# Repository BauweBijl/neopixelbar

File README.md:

# neopixelbar
Eagle files for a single sided 6 led's (WS2812B) PCB

This singlesided PCB design is for a neopixelbar with 6 WS2812B RGB led's (smd)...toner transfer method.

The WS2812B smd led's are soldered on the surface while the capacitors are tht and soldered on the bottom side of the board.

# Download and Print
Open the neonpixelbar.brd in Eagle and select the layers:

1. Top
2. Pads
3. Vias
4. Unrouted
5. Dimensions
6. Holes

Hit Ratsnest and print mirrored!

# Instructions
Build instructions with images follow later (todo)

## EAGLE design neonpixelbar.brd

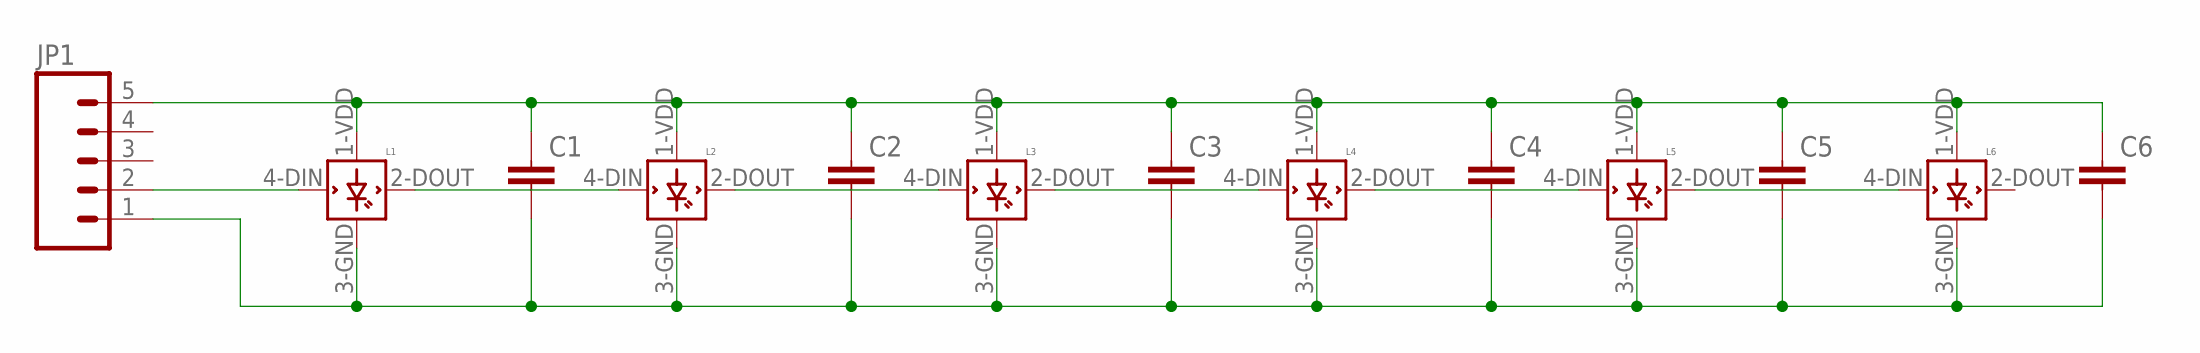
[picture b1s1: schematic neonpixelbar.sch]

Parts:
C1, C2, C3, C4, C5, C6: CAPPTH3; CAP-PTH-LARGE
JP1: M05PTH_LONGPADS; 1X05_LONGPADS
L1, L2, L3, L4, L5, L6: WS2812B

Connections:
GND: C1.2, C2.2, C3.2, C4.2, C5.2, C6.2, JP1.1, L1.3-GND (GND), L2.3-GND (GND), L3.3-GND (GND), L4.3-GND (GND), L5.3-GND (GND), L6.3-GND (GND)
unnamed: L1.2-DOUT (DOUT), L2.4-DIN (DIN)
unnamed: L2.2-DOUT (DOUT), L3.4-DIN (DIN)
unnamed: L3.2-DOUT (DOUT), L4.4-DIN (DIN)
unnamed: L4.2-DOUT (DOUT), L5.4-DIN (DIN)
unnamed: L5.2-DOUT (DOUT), L6.4-DIN (DIN)
unnamed: JP1.2, L1.4-DIN (DIN)
VDD: C1.1, C2.1, C3.1, C4.1, C5.1, C6.1, JP1.5, L1.1-VDD (VDD), L2.1-VDD (VDD), L3.1-VDD (VDD), L4.1-VDD (VDD), L5.1-VDD (VDD), L6.1-VDD (VDD)

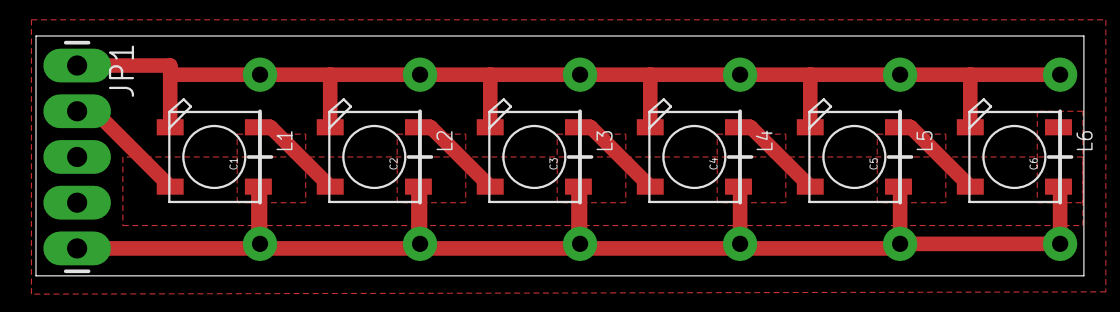
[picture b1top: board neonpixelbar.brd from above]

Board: 2 copper layers, 58.2 x 13.3 mm, 13 parts (0 on the bottom side), 8 nets.

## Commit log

2015-02-09 new file: neonpixelbar.brd new file: neonpixelbar.pdf new file: neonpixelbar.sch
2015-02-09 modified: README.md

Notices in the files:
parts and their libraries:
SparkFun-Capacitors: Licensing: Creative Commons ShareAlike 4.0 International - https://creativecommons.org/licenses/by-sa/4.0
